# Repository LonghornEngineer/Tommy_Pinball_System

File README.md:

Tommy_Pinball_System
====================

A Pinball System based off the Parallax Propeller. Aimed at hobby use. This project is mothballed. See the PinHeck for future development.

More information can be found on the Tommy project page.

http://longhornengineer.com/pinball/tommy-pinball-system/

Created by:
Parker Dillmann
The Longhorn Engineer

http://longhornengineer.com/

Disclaimer and licensing information can be found below.
http://longhornengineer.com/diy/disclaimer/

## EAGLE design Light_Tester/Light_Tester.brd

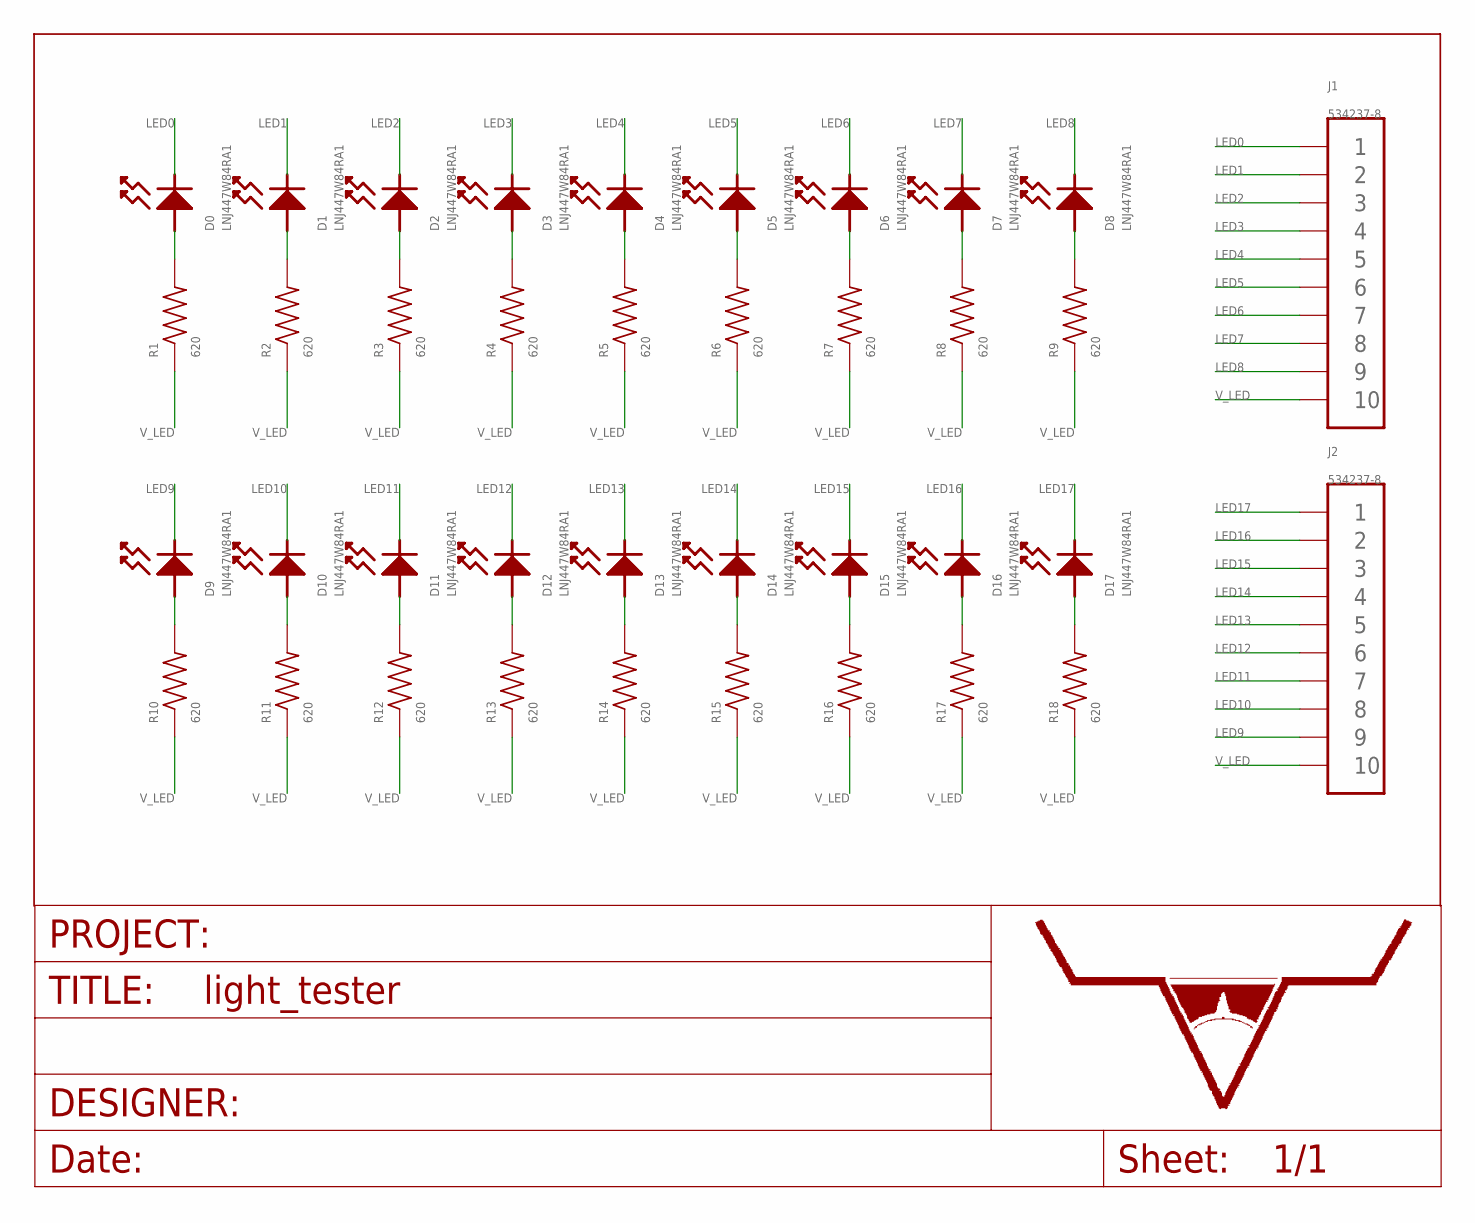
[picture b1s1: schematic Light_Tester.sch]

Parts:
D0, D1, D2, D3, D4, D5, D6, D7, D8, D9, D10, D11, D12, D13, D14, D15, D16, D17: LNJ447W84RA1; LED_0402
J1, J2: 534237-8; HEADER_01X10_PTH
R1, R2, R3, R4, R5, R6, R7, R8, R9, R10, R11, R12, R13, R14, R15, R16, R17, R18: 620; 0402
U$1: LHE_FRAME

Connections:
LED0: D0.CATHODE, J1.1
LED1: D1.CATHODE, J1.2
LED2: D2.CATHODE, J1.3
LED3: D3.CATHODE, J1.4
LED4: D4.CATHODE, J1.5
LED5: D5.CATHODE, J1.6
LED6: D6.CATHODE, J1.7
LED7: D7.CATHODE, J1.8
LED8: D8.CATHODE, J1.9
LED9: D9.CATHODE, J2.9
LED10: D10.CATHODE, J2.8
LED11: D11.CATHODE, J2.7
LED12: D12.CATHODE, J2.6
LED13: D13.CATHODE, J2.5
LED14: D14.CATHODE, J2.4
LED15: D15.CATHODE, J2.3
LED16: D16.CATHODE, J2.2
LED17: D17.CATHODE, J2.1
unnamed: D1.ANODE, R2.2
unnamed: D0.ANODE, R1.2
unnamed: D2.ANODE, R3.2
unnamed: D3.ANODE, R4.2
unnamed: D4.ANODE, R5.2
unnamed: D5.ANODE, R6.2
unnamed: D6.ANODE, R7.2
unnamed: D7.ANODE, R8.2
unnamed: D8.ANODE, R9.2
unnamed: D9.ANODE, R10.2
unnamed: D10.ANODE, R11.2
unnamed: D11.ANODE, R12.2
unnamed: D12.ANODE, R13.2
unnamed: D13.ANODE, R14.2
unnamed: D14.ANODE, R15.2
unnamed: D15.ANODE, R16.2
unnamed: D16.ANODE, R17.2
unnamed: D17.ANODE, R18.2
V_LED: J1.10, J2.10, R1.1, R2.1, R3.1, R4.1, R5.1, R6.1, R7.1, R8.1, R9.1, R10.1, R11.1, R12.1, R13.1, R14.1, R15.1, R16.1, R17.1, R18.1

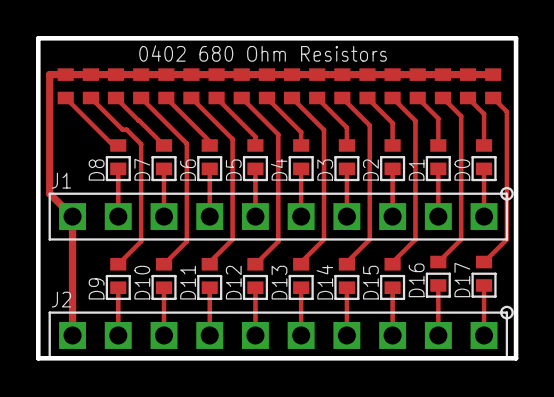
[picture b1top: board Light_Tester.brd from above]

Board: 4 copper layers, 26.5 x 17.8 mm, 39 parts (1 on the bottom side), 37 nets.

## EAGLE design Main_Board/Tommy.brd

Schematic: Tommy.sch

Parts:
ANALOG_0, ANALOG_1, ANALOG_2, ANALOG_3: PH_1X03HEADER_PTH; HEADER_01X03_PTH
AUDIO: 161-3507-E
AUX: 103169-5; HEADER_02X07_PTH
C1, C2, C3, C4, C5, C6, C7, C8, C9, C10, C11, C12, C13, C14, C15, C16, C17, C18, C19, C20, C21, C22, C23, C24, C25, C26, C27, C28, C29, C30, C31, C36, C41, C44, C45, C46, C47, C48, C49, C50, C51, C52, C53, C58, C59, C61: .1uF; 0402
C32, C37, C54: 2.2uF; 1206_POLARIZED
C33, C38, C55: 10uF; 1206_POLARIZED
C34, C39, C56, C65: 100uF; 6.3MM_CAP_SMD
C35, C40, C42, C43, C57, C60, C66, C67, C68, C69: 1uF; 0402
C62, C63, C64: ULR2C390MNL1GS; EEH-ZA1V271P
D1, D2, D3, D4, D5: LEDSML0603; SML0603
DMD_CONN: 103169-5; HEADER_02X07_PTH
DMD_PWR: PH_1X02MOLEX_26-61-4020; MOLEX_KK_2
EM1: SPDT_RELAYG5LA; G5LA_PCBRELAY_SPDT
FUSE: 4245K
INPUT_BANK_0, INPUT_BANK_1, INPUT_BANK_2, INPUT_BANK_3, INPUT_BANK_4, INPUT_BANK_5, INPUT_BANK_6, INPUT_BANK_7: 5-103669-8; HEADER_01X09_PTH
J35, J36: ROYS_VOLTAGE_CHOOSER
LIGHT_BANK_0, LIGHT_BANK_1, LIGHT_BANK_2, LIGHT_BANK_3, LIGHT_BANK_4, LIGHT_BANK_5, LIGHT_BANK_6, LIGHT_BANK_7: 103414-8; HEADER_01X10_PTH
OUTPUT_BANK_0, OUTPUT_BANK_1, OUTPUT_BANK_2, OUTPUT_BANK_3: 26-61-4090; MOLEX_KK_9
PC_POWER_SUPPLY: MOLEX_39-29-9202
R1, R2, R3, R186, R187: 330; 0402
R4, R5, R6, R7, R8, R9, R10, R11, R15, R16, R17, R18, R19, R20, R21, R22, R23, R24, R25, R26, R27, R28, R29, R30, R31, R32, R33, R34, R35, R36, R37, R38, R39, R40, R41, R42, R43, R44, R45, R46, R176, R179, R189: 10K; 0402
R12, R13, R14, R175: 1.25K; 0402
R47, R48, R49, R50, R55, R56, R57, R58, R63, R64, R65, R66, R71, R72, R73, R74, R79, R80, R81, R82, R87, R88, R89, R90, R95, R96, R97, R98, R103, R104, R105, R106, R111, R112, R113, R114, R119, R120, R121, R122, R127, R128, R129, R130, R135, R136, R137, R138, R143, R144, R145, R146, R151, R152, R153, R154, R159, R160, R161, R162, R167, R168, R169, R170: 180; 0402
R51, R52, R53, R54, R59, R60, R61, R62, R67, R68, R69, R70, R75, R76, R77, R78, R83, R84, R85, R86, R91, R92, R93, R94, R99, R100, R101, R102, R107, R108, R109, R110, R115, R116, R117, R118, R123, R124, R125, R126, R131, R132, R133, R134, R139, R140, R141, R142, R147, R148, R149, R150, R155, R156, R157, R158, R163, R164, R165, R166, R171, R172, R173, R174: 100; 0402
R177, R178, R188: 1K; 0402
R180, R181: 22; 0402
R182, R183: 0; 0402
RESET: 101-0134-EV
RGB_CONN: PH_1X04HEADER_PTH_ROUND; HEADER_01X04_PTH_ROUND
S0, S1, S2, S3, S4, S5, S6, S7, S8, S9, S10, S11, S12, S13, S14, S15, S16, S17, S18, S19, S20, S21, S22, S23, S24, S25, S26, S27, S28, S29, S30, S31: RFP12N10L; TO-220AB
SD1: 502570-0893
SEG1, SEG2, SEG3: LSHD-A103
SERVO_0, SERVO_1, SERVO_2, SERVO_3, SERVO_4, SERVO_5, SERVO_6, SERVO_7: PH_1X03HEADER_PTH; HEADER_01X03_PTH
SERVO_EXT_PWR: 26-61-4020; MOLEX_KK_2
SOLENOID_PWR: 26-61-4020; MOLEX_KK_4
SW2: 0S102011MS2QS1
U1: P8X32A-Q44; LQFP-44
U2: FT230X; SSOP-16
U3, U75, U76, U77, U78, U79, U80, U82: IP4234CZ6; SOT-457
U4: CAT24M01XI-T2; SOIC-8_W
U5, U6, U7, U8, U39, U40, U41, U42: 74HC595D-Q100; TTSOP-16
U9, U10, U11, U12, U13, U14, U15, U16: SN74HC165QPWRG4Q1; TTSOP-16
U17, U18, U19, U38: WS2803; SOP-28
U20, U21, U22, U23, U24, U25, U26, U27, U28, U29, U30, U31, U32, U33, U34, U35: TCMT4100; SOP-16
U36, U37: 23LC1024-I/ST; TTSOP-8
U81: MIC1832MY; SOIC-8
U83: AD7991YRJZ-0500RL7; SOT-23-8
U84: MMBT 3904 LT1; SOT-23
U$1: LHE_FRAME
USB: 10118193-0001LF
X1: ABMM-6.000MHZ-B2-T; 7MM_X_5MM

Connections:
3.3V: ANALOG_0.3, ANALOG_1.3, ANALOG_2.3, ANALOG_3.3, AUX.1, C3.2, C4.2, C5.2, C6.2, C8.2, C9.2, C10.2, C11.2, C12.2, C13.2, C14.2, C15.2, C16.2, C17.2, C18.2, C19.2, C20.2, C21.1, C22.2, C23.2, C24.2, C25.2, C26.2, C27.2, C28.2, C29.2, C30.2, C31.2, C32.+ (POS), C33.+ (POS), C34.POS, C35.1, C36.1, C59.2, C60.2, C61.2, EM1.2, J35.1, PC_POWER_SUPPLY.1, PC_POWER_SUPPLY.2, PC_POWER_SUPPLY.3, R4.2, R5.2, R6.2, R7.2, R8.2, R9.2, R10.2, R11.2, R176.2, R186.2, RGB_CONN.4, SD1.5 (3.3V), U1.8 (VDD), U1.18 (VDD), U1.30 (VDD), U1.40 (VDD), U4.8 (VCC), U5.10 (MR), U5.16 (VCC), U6.10 (MR), U6.16 (VCC), U7.10 (MR), U7.16 (VCC), U8.10 (MR), U8.16 (VCC), U9.16 (VCC), U10.16 (VCC), U11.16 (VCC), U12.16 (VCC), U13.16 (VCC), U14.16 (VCC), U15.16 (VCC), U16.16 (VCC), U17.28 (VCC), U18.28 (VCC), U19.28 (VCC), U20.10 (CO3), U20.12 (CO2), U20.14 (CO1), U20.16 (CO0), U21.10 (CO3), U21.12 (CO2), U21.14 (CO1), U21.16 (CO0), U22.10 (CO3), U22.12 (CO2), U22.14 (CO1), U22.16 (CO0), U23.10 (CO3), U23.12 (CO2), U23.14 (CO1), U23.16 (CO0), U24.10 (CO3), U24.12 (CO2), U24.14 (CO1), U24.16 (CO0), U25.10 (CO3), U25.12 (CO2), U25.14 (CO1), U25.16 (CO0), U26.10 (CO3), U26.12 (CO2), U26.14 (CO1), U26.16 (CO0), U27.10 (CO3), U27.12 (CO2), U27.14 (CO1), U27.16 (CO0), U28.10 (CO3), U28.12 (CO2), U28.14 (CO1), U28.16 (CO0), U29.10 (CO3), U29.12 (CO2), U29.14 (CO1), U29.16 (CO0), U30.10 (CO3), U30.12 (CO2), U30.14 (CO1), U30.16 (CO0), U31.10 (CO3), U31.12 (CO2), U31.14 (CO1), U31.16 (CO0), U32.10 (CO3), U32.12 (CO2), U32.14 (CO1), U32.16 (CO0), U33.10 (CO3), U33.12 (CO2), U33.14 (CO1), U33.16 (CO0), U34.10 (CO3), U34.12 (CO2), U34.14 (CO1), U34.16 (CO0), U35.10 (CO3), U35.12 (CO2), U35.14 (CO1), U35.16 (CO0), U36.8 (VCC), U37.8 (VCC), U38.28 (VCC), U39.10 (MR), U39.16 (VCC), U40.10 (MR), U40.16 (VCC), U41.10 (MR), U41.16 (VCC), U42.10 (MR), U42.16 (VCC), U75.5 (VB), U76.5 (VB), U77.5 (VB), U78.5 (VB), U79.5 (VB), U80.5 (VB), U81.2 (TD), U81.3 (TOL), U81.8 (VCC), U82.5 (VB), U83.8 (VCC)
3V3OUT: C2.1, U2.3 (VCCIO), U2.10 (3V3OUT), U2.11 (RESET#)
5V: C37.+ (POS), C38.+ (POS), C39.POS, C40.1, C41.1, DMD_PWR.P$2 (2), J35.2, J36.1, PC_POWER_SUPPLY.7, PC_POWER_SUPPLY.11, PC_POWER_SUPPLY.18, PC_POWER_SUPPLY.20
12V: C46.2, C47.2, C48.2, C49.2, C50.2, C51.2, C52.2, C53.2, C54.+ (POS), C55.+ (POS), C56.POS, C57.1, C58.1, INPUT_BANK_0.9, INPUT_BANK_1.9, INPUT_BANK_2.9, INPUT_BANK_3.9, INPUT_BANK_4.9, INPUT_BANK_5.9, INPUT_BANK_6.9, INPUT_BANK_7.9, J35.3, J36.3, PC_POWER_SUPPLY.19
-5V: PC_POWER_SUPPLY.16
-12V: PC_POWER_SUPPLY.4
AUDIO_L: R177.1, U1.33 (P26)
AUDIO_OUT_L: AUDIO.5 (T), C42.1
AUDIO_OUT_R: AUDIO.2 (R), C43.1
AUDIO_R: R178.1, U1.34 (P27)
AUD_L_FILTER: C42.2, C44.1, R177.2
AUD_R_FILTER: C43.2, C45.2, R178.2
A_0: ANALOG_0.1, U83.3 (A_0)
A_1: ANALOG_1.1, U83.4 (A_1)
A_2: ANALOG_2.1, U83.5 (A_2)
A_3: ANALOG_3.1, U83.6 (A_3)
C0: R47.1, U20.2 (C0)
C1: R48.1, U20.4 (C1)
C2: R49.1, U20.6 (C2)
C3: R50.1, U20.8 (C3)
C4: R55.1, U21.2 (C0)
C5: R56.1, U21.4 (C1)
C6: R57.1, U21.6 (C2)
C7: R58.1, U21.8 (C3)
C8: R63.1, U22.2 (C0)
C9: R64.1, U22.4 (C1)
C10: R65.1, U22.6 (C2)
C11: R66.1, U22.8 (C3)
C12: R71.1, U23.2 (C0)
C13: R72.1, U23.4 (C1)
C14: R73.1, U23.6 (C2)
C15: R74.1, U23.8 (C3)
C16: R79.1, U24.2 (C0)
C17: R80.1, U24.4 (C1)
C18: R81.1, U24.6 (C2)
C19: R82.1, U24.8 (C3)
C20: R87.1, U25.2 (C0)
C21: R88.1, U25.4 (C1)
C22: R89.1, U25.6 (C2)
C23: R90.1, U25.8 (C3)
C24: R95.1, U26.2 (C0)
C25: R96.1, U26.4 (C1)
C26: R97.1, U26.6 (C2)
C27: R98.1, U26.8 (C3)
C28: R103.1, U27.2 (C0)
C29: R104.1, U27.4 (C1)
C30: R105.1, U27.6 (C2)
C31: R106.1, U27.8 (C3)
C32: R111.1, U28.2 (C0)
C33: R112.1, U28.4 (C1)
C34: R113.1, U28.6 (C2)
C35: R114.1, U28.8 (C3)
C36: R119.1, U29.2 (C0)
C37: R120.1, U29.4 (C1)
C38: R121.1, U29.6 (C2)
C39: R122.1, U29.8 (C3)
C40: R127.1, U30.2 (C0)
C41: R128.1, U30.4 (C1)
C42: R129.1, U30.6 (C2)
C43: R130.1, U30.8 (C3)
C44: R135.1, U31.2 (C0)
C45: R136.1, U31.4 (C1)
C46: R137.1, U31.6 (C2)
C47: R138.1, U31.8 (C3)
C48: R143.1, U32.2 (C0)
C49: R144.1, U32.4 (C1)
C50: R145.1, U32.6 (C2)
C51: R146.1, U32.8 (C3)
C52: R151.1, U33.2 (C0)
C53: R152.1, U33.4 (C1)
C54: R153.1, U33.6 (C2)
C55: R154.1, U33.8 (C3)
C56: R159.1, U34.2 (C0)
C57: R160.1, U34.4 (C1)
C58: R161.1, U34.6 (C2)
C59: R162.1, U34.8 (C3)
C60: R167.1, U35.2 (C0)
C61: R168.1, U35.4 (C1)
C62: R169.1, U35.6 (C2)
C63: R170.1, U35.8 (C3)
D1: D1.C, R1.2
D2: D2.C, R2.2
D3: D3.C, R3.2
D+: U3.1 (I/O1A), USB.3 (D+)
D-: U3.6 (I/O1B), USB.2 (D-)
DATA_CLK: U1.3 (P6), U5.12 (STCP), U6.12 (STCP), U7.12 (STCP), U8.12 (STCP), U9.2 (CLK), U10.2 (CLK), U11.2 (CLK), U12.2 (CLK), U13.2 (CLK), U14.2 (CLK), U15.2 (CLK), U16.2 (CLK), U39.12 (STCP), U40.12 (STCP), U41.12 (STCP), U42.12 (STCP), U80.4 (I/O2B), U81.7 (/ST)
DATA_CLK_OUT: AUX.3, U80.6 (I/O1B)
DATA_IN: U1.2 (P5), U9.9 (QH)
DATA_IN1: U9.10 (SER), U10.9 (QH)
DATA_IN2: U10.10 (SER), U11.9 (QH)
DATA_IN3: U11.10 (SER), U12.9 (QH)
DATA_IN4: U12.10 (SER), U13.9 (QH)
DATA_IN5: U13.10 (SER), U14.9 (QH)
DATA_IN6: U14.10 (SER), U15.9 (QH)
DATA_IN7: U15.10 (SER), U16.9 (QH)
DATA_IN8: U16.10 (SER), U79.4 (I/O2B)
DATA_IN8_OUT: AUX.5, U79.6 (I/O1B)
DATA_LAT: U1.4 (P7), U5.11 (SHCP), U6.11 (SHCP), U7.11 (SHCP), U8.11 (SHCP), U9.1 (LAT), U10.1 (LAT), U11.1 (LAT), U12.1 (LAT), U13.1 (LAT), U14.1 (LAT), U15.1 (LAT), U16.1 (LAT), U39.11 (SHCP), U40.11 (SHCP), U41.11 (SHCP), U42.11 (SHCP), U80.3 (I/O2A)
DATA_LAT_OUT: AUX.2, U80.1 (I/O1A)
DATA_OUT: U1.1 (P4), U5.14 (DS)
DATA_OUT1: U5.9 (Q7S), U6.14 (DS)
DATA_OUT2: U6.9 (Q7S), U7.14 (DS)
DATA_OUT3: U7.9 (Q7S), U8.14 (DS)
DATA_OUT4: U8.9 (Q7S), U39.14 (DS)
DATA_OUT5: U39.9 (Q7S), U40.14 (DS)
DATA_OUT6: U40.9 (Q7S), U41.14 (DS)
DATA_OUT7: U41.9 (Q7S), U42.14 (DS)
DATA_OUT8: U42.9 (Q7S), U79.3 (I/O2A)
DATA_OUT8_OUT: AUX.4, U79.1 (I/O1A)
DM: R180.2, U3.4 (I/O2B)
DMD0: U1.14 (P13), U78.3 (I/O2A)
DMD1: U1.13 (P12), U78.4 (I/O2B)
DMD2: U1.12 (P11), U77.3 (I/O2A)
DMD3: U1.11 (P10), U77.4 (I/O2B)
DMD4: U1.10 (P9), U76.3 (I/O2A)
DMD5: U1.9 (P8), U76.4 (I/O2B)
DMD_OUT0: DMD_CONN.1, U78.1 (I/O1A)
DMD_OUT1: DMD_CONN.2, U78.6 (I/O1B)
DMD_OUT2: DMD_CONN.3, U77.1 (I/O1A)
DMD_OUT3: DMD_CONN.4, U77.6 (I/O1B)
DMD_OUT4: DMD_CONN.5, U76.1 (I/O1A)
DMD_OUT5: DMD_CONN.6, U76.6 (I/O1B)
DP: R181.2, U3.3 (I/O2A)
GND: ANALOG_0.2, ANALOG_1.2, ANALOG_2.2, ANALOG_3.2, AUDIO.1 (S), AUX.8, AUX.9, AUX.10, AUX.11, AUX.12, AUX.13, AUX.14, C1.2, C2.2, C3.1, C4.1, C5.1, C6.1, C8.1, C9.1, C10.1, C11.1, C12.1, C13.1, C14.1, C15.1, C16.1, C17.1, C18.1, C19.1, C20.1, C21.2, C22.1, C23.1, C24.1, C25.1, C26.1, C27.1, C28.1, C29.1, C30.1, C31.1, C32.- (NEG), C33.- (NEG), C34.NEG, C35.2, C36.2, C37.- (NEG), C38.- (NEG), C39.NEG, C40.2, C41.2, C44.2, C45.1, C46.1, C47.1, C48.1, C49.1, C50.1, C51.1, C52.1, C53.1, C54.- (NEG), C55.- (NEG), C56.NEG, C57.2, C58.2, C59.1, C60.1, C61.1, C65.NEG, C66.1, C67.1, C68.1, C69.1, D4.C, DMD_CONN.8, DMD_CONN.9, DMD_CONN.10, DMD_CONN.11, DMD_CONN.12, DMD_CONN.13, DMD_CONN.14, DMD_PWR.P$1 (1), PC_POWER_SUPPLY.5, PC_POWER_SUPPLY.6, PC_POWER_SUPPLY.9, PC_POWER_SUPPLY.10, PC_POWER_SUPPLY.12, PC_POWER_SUPPLY.13, PC_POWER_SUPPLY.14, R1.1, R12.2, R13.2, R14.2, R15.1, R16.1, R17.1, R18.1, R19.1, R20.1, R21.1, R22.1, R23.1, R24.1, R25.1, R26.1, R27.1, R28.1, R29.1, R30.1, R31.1, R32.1, R33.1, R34.1, R35.1, R36.1, R37.1, R38.1, R39.1, R40.1, R41.1, R42.1, R43.1, R44.1, R45.1, R46.1, R47.2, R48.2, R49.2, R50.2, R51.1, R52.1, R53.1, R54.1, R55.2, R56.2, R57.2, R58.2, R59.1, R60.1, R61.1, R62.1, R63.2, R64.2, R65.2, R66.2, R67.1, R68.1, R69.1, R70.1, R71.2, R72.2, R73.2, R74.2, R75.1, R76.1, R77.1, R78.1, R79.2, R80.2, R81.2, R82.2, R83.1, R84.1, R85.1, R86.1, R87.2, R88.2, R89.2, R90.2, R91.1, R92.1, R93.1, R94.1, R95.2, R96.2, R97.2, R98.2, R99.1, R100.1, R101.1, R102.1, R103.2, R104.2, R105.2, R106.2, R107.1, R108.1, R109.1, R110.1, R111.2, R112.2, R113.2, R114.2, R115.1, R116.1, R117.1, R118.1, R119.2, R120.2, R121.2, R122.2, R123.1, R124.1, R125.1, R126.1, R127.2, R128.2, R129.2, R130.2, R131.1, R132.1, R133.1, R134.1, R135.2, R136.2, R137.2, R138.2, R139.1, R140.1, R141.1, R142.1, R143.2, R144.2, R145.2, R146.2, R147.1, R148.1, R149.1, R150.1, R151.2, R152.2, R153.2, R154.2, R155.1, R156.1, R157.1, R158.1, R159.2, R160.2, R161.2, R162.2, R163.1, R164.1, R165.1, R166.1, R167.2, R168.2, R169.2, R170.2, R171.1, R172.1, R173.1, R174.1, R175.2, R179.2, R182.2, R183.2, R187.1, R189.2, RESET.1 (A), RGB_CONN.3, SD1.3 (GND), SD1.SHIELD0 (GND), SD1.SHIELD1 (GND), SD1.SHIELD2 (GND), SD1.SHIELD3 (GND), SEG1.1 (COM), SEG1.6 (COM), SEG2.1 (COM), SEG2.6 (COM), SEG3.1 (COM), SEG3.6 (COM), SERVO_0.3, SERVO_1.3, SERVO_2.3, SERVO_3.3, SERVO_4.3, SERVO_5.3, SERVO_6.3, SERVO_7.3, SERVO_EXT_PWR.P$1 (1), SW2.1, U1.5 (VSS), U1.6 (BOE'), U1.17 (VSS), U1.27 (VSS), U1.39 (VSS), U2.5 (GND), U2.13 (GND), U3.2 (GND), U4.2 (A1), U4.3 (A2), U4.4 (GND), U4.7 (WP), U5.8 (GND), U6.8 (GND), U7.8 (GND), U8.8 (GND), U9.8 (GND), U9.15 (C_INH), U10.8 (GND), U10.15 (C_INH), U11.8 (GND), U11.15 (C_INH), U12.8 (GND), U12.15 (C_INH), U13.8 (GND), U13.15 (C_INH), U14.8 (GND), U14.15 (C_INH), U15.8 (GND), U15.15 (C_INH), U16.8 (GND), U16.15 (C_INH), U17.1 (GND), U18.1 (GND), U19.1 (GND), U36.1 (CS'), U36.4 (GND), U37.1 (CS'), U37.4 (GND), U38.1 (GND), U39.8 (GND), U40.8 (GND), U41.8 (GND), U42.8 (GND), U75.2 (GND), U76.2 (GND), U77.2 (GND), U78.2 (GND), U79.2 (GND), U80.2 (GND), U81.4 (GND), U82.2 (GND), U83.7 (GND), U84.2 (EMITTER), USB.5 (GND), USB.S1 (GND), USB.S2 (GND), USB.S3 (GND), USB.S4 (GND)
IN0: R51.2, U9.11 (D0), U20.15 (E0)
IN1: R52.2, U9.12 (D1), U20.13 (E1)
IN2: R53.2, U9.13 (D2), U20.11 (E2)
IN3: R54.2, U9.14 (D3), U20.9 (E3)
IN4: R59.2, U9.3 (D4), U21.15 (E0)
IN5: R60.2, U9.4 (D5), U21.13 (E1)
IN6: R61.2, U9.5 (D6), U21.11 (E2)
IN7: R62.2, U9.6 (D7), U21.9 (E3)
IN8: R67.2, U10.11 (D0), U22.15 (E0)
IN9: R68.2, U10.12 (D1), U22.13 (E1)
IN10: R69.2, U10.13 (D2), U22.11 (E2)
IN11: R70.2, U10.14 (D3), U22.9 (E3)
IN12: R75.2, U10.3 (D4), U23.15 (E0)
IN13: R76.2, U10.4 (D5), U23.13 (E1)
IN14: R77.2, U10.5 (D6), U23.11 (E2)
IN15: R78.2, U10.6 (D7), U23.9 (E3)
IN16: R83.2, U11.11 (D0), U24.15 (E0)
IN17: R84.2, U11.12 (D1), U24.13 (E1)
IN18: R85.2, U11.13 (D2), U24.11 (E2)
IN19: R86.2, U11.14 (D3), U24.9 (E3)
IN20: R91.2, U11.3 (D4), U25.15 (E0)
IN21: R92.2, U11.4 (D5), U25.13 (E1)
IN22: R93.2, U11.5 (D6), U25.11 (E2)
IN23: R94.2, U11.6 (D7), U25.9 (E3)
IN24: R99.2, U12.11 (D0), U26.15 (E0)
IN25: R100.2, U12.12 (D1), U26.13 (E1)
IN26: R101.2, U12.13 (D2), U26.11 (E2)
IN27: R102.2, U12.14 (D3), U26.9 (E3)
IN28: R107.2, U12.3 (D4), U27.15 (E0)
IN29: R108.2, U12.4 (D5), U27.13 (E1)
IN30: R109.2, U12.5 (D6), U27.11 (E2)
IN31: R110.2, U12.6 (D7), U27.9 (E3)
IN32: R115.2, U13.11 (D0), U28.15 (E0)
IN33: R116.2, U13.12 (D1), U28.13 (E1)
IN34: R117.2, U13.13 (D2), U28.11 (E2)
IN35: R118.2, U13.14 (D3), U28.9 (E3)
IN36: R123.2, U13.3 (D4), U29.15 (E0)
IN37: R124.2, U13.4 (D5), U29.13 (E1)
IN38: R125.2, U13.5 (D6), U29.11 (E2)
IN39: R126.2, U13.6 (D7), U29.9 (E3)
IN40: R131.2, U14.11 (D0), U30.15 (E0)
IN41: R132.2, U14.12 (D1), U30.13 (E1)
IN42: R133.2, U14.13 (D2), U30.11 (E2)
IN43: R134.2, U14.14 (D3), U30.9 (E3)
IN44: R139.2, U14.3 (D4), U31.15 (E0)
IN45: R140.2, U14.4 (D5), U31.13 (E1)
IN46: R141.2, U14.5 (D6), U31.11 (E2)
IN47: R142.2, U14.6 (D7), U31.9 (E3)
IN48: R147.2, U15.11 (D0), U32.15 (E0)
IN49: R148.2, U15.12 (D1), U32.13 (E1)
IN50: R149.2, U15.13 (D2), U32.11 (E2)
IN51: R150.2, U15.14 (D3), U32.9 (E3)
IN52: R155.2, U15.3 (D4), U33.15 (E0)
IN53: R156.2, U15.4 (D5), U33.13 (E1)
IN54: R157.2, U15.5 (D6), U33.11 (E2)
IN55: R158.2, U15.6 (D7), U33.9 (E3)
IN56: R163.2, U16.11 (D0), U34.15 (E0)
IN57: R164.2, U16.12 (D1), U34.13 (E1)
IN58: R165.2, U16.13 (D2), U34.11 (E2)
IN59: R166.2, U16.14 (D3), U34.9 (E3)
IN60: R171.2, U16.3 (D4), U35.15 (E0)
IN61: R172.2, U16.4 (D5), U35.13 (E1)
IN62: R173.2, U16.5 (D6), U35.11 (E2)
IN63: R174.2, U16.6 (D7), U35.9 (E3)
INPUT0: INPUT_BANK_0.1, U20.1 (A0)
INPUT1: INPUT_BANK_0.2, U20.3 (A1)
INPUT2: INPUT_BANK_0.3, U20.5 (A2)
INPUT3: INPUT_BANK_0.4, U20.7 (A3)
INPUT4: INPUT_BANK_0.5, U21.1 (A0)
INPUT5: INPUT_BANK_0.6, U21.3 (A1)
INPUT6: INPUT_BANK_0.7, U21.5 (A2)
INPUT7: INPUT_BANK_0.8, U21.7 (A3)
INPUT8: INPUT_BANK_1.1, U22.1 (A0)
INPUT9: INPUT_BANK_1.2, U22.3 (A1)
INPUT10: INPUT_BANK_1.3, U22.5 (A2)
INPUT11: INPUT_BANK_1.4, U22.7 (A3)
INPUT12: INPUT_BANK_1.5, U23.1 (A0)
INPUT13: INPUT_BANK_1.6, U23.3 (A1)
INPUT14: INPUT_BANK_1.7, U23.5 (A2)
INPUT15: INPUT_BANK_1.8, U23.7 (A3)
INPUT16: INPUT_BANK_2.1, U24.1 (A0)
INPUT17: INPUT_BANK_2.2, U24.3 (A1)
INPUT18: INPUT_BANK_2.3, U24.5 (A2)
INPUT19: INPUT_BANK_2.4, U24.7 (A3)
INPUT20: INPUT_BANK_2.5, U25.1 (A0)
INPUT21: INPUT_BANK_2.6, U25.3 (A1)
INPUT22: INPUT_BANK_2.7, U25.5 (A2)
INPUT23: INPUT_BANK_2.8, U25.7 (A3)
INPUT24: INPUT_BANK_3.1, U26.1 (A0)
INPUT25: INPUT_BANK_3.2, U26.3 (A1)
INPUT26: INPUT_BANK_3.3, U26.5 (A2)
INPUT27: INPUT_BANK_3.4, U26.7 (A3)
INPUT28: INPUT_BANK_3.5, U27.1 (A0)
INPUT29: INPUT_BANK_3.6, U27.3 (A1)
INPUT30: INPUT_BANK_3.7, U27.5 (A2)
INPUT31: INPUT_BANK_3.8, U27.7 (A3)
INPUT32: INPUT_BANK_4.1, U28.1 (A0)
INPUT33: INPUT_BANK_4.2, U28.3 (A1)
INPUT34: INPUT_BANK_4.3, U28.5 (A2)
INPUT35: INPUT_BANK_4.4, U28.7 (A3)
INPUT36: INPUT_BANK_4.5, U29.1 (A0)
INPUT37: INPUT_BANK_4.6, U29.3 (A1)
INPUT38: INPUT_BANK_4.7, U29.5 (A2)
INPUT39: INPUT_BANK_4.8, U29.7 (A3)
INPUT40: INPUT_BANK_5.1, U30.1 (A0)
INPUT41: INPUT_BANK_5.2, U30.3 (A1)
INPUT42: INPUT_BANK_5.3, U30.5 (A2)
INPUT43: INPUT_BANK_5.4, U30.7 (A3)
INPUT44: INPUT_BANK_5.5, U31.1 (A0)
INPUT45: INPUT_BANK_5.6, U31.3 (A1)
INPUT46: INPUT_BANK_5.7, U31.5 (A2)
INPUT47: INPUT_BANK_5.8, U31.7 (A3)
INPUT48: INPUT_BANK_6.1, U32.1 (A0)
INPUT49: INPUT_BANK_6.2, U32.3 (A1)
INPUT50: INPUT_BANK_6.3, U32.5 (A2)
INPUT51: INPUT_BANK_6.4, U32.7 (A3)
INPUT52: INPUT_BANK_6.5, U33.1 (A0)
INPUT53: INPUT_BANK_6.6, U33.3 (A1)
INPUT54: INPUT_BANK_6.7, U33.5 (A2)
INPUT55: INPUT_BANK_6.8, U33.7 (A3)
INPUT56: INPUT_BANK_7.1, U34.1 (A0)
INPUT57: INPUT_BANK_7.2, U34.3 (A1)
INPUT58: INPUT_BANK_7.3, U34.5 (A2)
INPUT59: INPUT_BANK_7.4, U34.7 (A3)
INPUT60: INPUT_BANK_7.5, U35.1 (A0)
INPUT61: INPUT_BANK_7.6, U35.3 (A1)
INPUT62: INPUT_BANK_7.7, U35.5 (A2)
INPUT63: INPUT_BANK_7.8, U35.7 (A3)
IREF0: R12.1, U17.3 (IREF)
IREF1: R13.1, U18.3 (IREF)
IREF2: R14.1, U19.3 (IREF)
IREF3: R175.1, U38.3 (IREF)
IRQ: R6.1, SD1.1 (IRQ)
LED0: LIGHT_BANK_0.1, U17.6 (OUT0)
LED1: LIGHT_BANK_0.2, U17.7 (OUT1)
LED2: LIGHT_BANK_0.3, U17.8 (OUT2)
LED3: LIGHT_BANK_0.4, U17.9 (OUT3)
LED4: LIGHT_BANK_0.5, U17.10 (OUT4)
LED5: LIGHT_BANK_0.6, U17.11 (OUT5)
LED6: LIGHT_BANK_0.7, U17.12 (OUT6)
LED7: LIGHT_BANK_0.8, U17.13 (OUT7)
LED8: LIGHT_BANK_0.9, U17.14 (OUT8)
LED9: LIGHT_BANK_1.9, U17.15 (OUT9)
LED10: LIGHT_BANK_1.8, U17.16 (OUT10)
LED11: LIGHT_BANK_1.7, U17.17 (OUT11)
LED12: LIGHT_BANK_1.6, U17.18 (OUT12)
LED13: LIGHT_BANK_1.5, U17.19 (OUT13)
LED14: LIGHT_BANK_1.4, U17.20 (OUT14)
LED15: LIGHT_BANK_1.3, U17.21 (OUT15)
LED16: LIGHT_BANK_1.2, U17.22 (OUT16)
LED17: LIGHT_BANK_1.1, U17.23 (OUT17)
LED18: LIGHT_BANK_2.1, U18.6 (OUT0)
LED19: LIGHT_BANK_2.2, U18.7 (OUT1)
LED20: LIGHT_BANK_2.3, U18.8 (OUT2)
LED21: LIGHT_BANK_2.4, U18.9 (OUT3)
LED22: LIGHT_BANK_2.5, U18.10 (OUT4)
LED23: LIGHT_BANK_2.6, U18.11 (OUT5)
LED24: LIGHT_BANK_2.7, U18.12 (OUT6)
LED25: LIGHT_BANK_2.8, U18.13 (OUT7)
LED26: LIGHT_BANK_2.9, U18.14 (OUT8)
LED27: LIGHT_BANK_3.9, U18.15 (OUT9)
LED28: LIGHT_BANK_3.8, U18.16 (OUT10)
LED29: LIGHT_BANK_3.7, U18.17 (OUT11)
LED30: LIGHT_BANK_3.6, U18.18 (OUT12)
LED31: LIGHT_BANK_3.5, U18.19 (OUT13)
LED32: LIGHT_BANK_3.4, U18.20 (OUT14)
LED33: LIGHT_BANK_3.3, U18.21 (OUT15)
LED34: LIGHT_BANK_3.2, U18.22 (OUT16)
LED35: LIGHT_BANK_3.1, U18.23 (OUT17)
LED36: LIGHT_BANK_4.1, U19.6 (OUT0)
LED37: LIGHT_BANK_4.2, U19.7 (OUT1)
LED38: LIGHT_BANK_4.3, U19.8 (OUT2)
LED39: LIGHT_BANK_4.4, U19.9 (OUT3)
LED40: LIGHT_BANK_4.5, U19.10 (OUT4)
LED41: LIGHT_BANK_4.6, U19.11 (OUT5)
LED42: LIGHT_BANK_4.7, U19.12 (OUT6)
LED43: LIGHT_BANK_4.8, U19.13 (OUT7)
LED44: LIGHT_BANK_4.9, U19.14 (OUT8)
LED45: LIGHT_BANK_5.9, U19.15 (OUT9)
LED46: LIGHT_BANK_5.8, U19.16 (OUT10)
LED47: LIGHT_BANK_5.7, U19.17 (OUT11)
LED48: LIGHT_BANK_5.6, U19.18 (OUT12)
LED49: LIGHT_BANK_5.5, U19.19 (OUT13)
LED50: LIGHT_BANK_5.4, U19.20 (OUT14)
LED51: LIGHT_BANK_5.3, U19.21 (OUT15)
LED52: LIGHT_BANK_5.2, U19.22 (OUT16)
LED53: LIGHT_BANK_5.1, U19.23 (OUT17)
LED54: LIGHT_BANK_6.1, U38.6 (OUT0)
LED55: LIGHT_BANK_6.2, U38.7 (OUT1)
LED56: LIGHT_BANK_6.3, U38.8 (OUT2)
LED57: LIGHT_BANK_6.4, U38.9 (OUT3)
LED58: LIGHT_BANK_6.5, U38.10 (OUT4)
LED59: LIGHT_BANK_6.6, U38.11 (OUT5)
LED60: LIGHT_BANK_6.7, U38.12 (OUT6)
LED61: LIGHT_BANK_6.8, U38.13 (OUT7)
LED62: LIGHT_BANK_6.9, U38.14 (OUT8)
LED63: LIGHT_BANK_7.9, U38.15 (OUT9)
LED64: LIGHT_BANK_7.8, U38.16 (OUT10)
LED65: LIGHT_BANK_7.7, U38.17 (OUT11)
LED66: LIGHT_BANK_7.6, U38.18 (OUT12)
LED67: LIGHT_BANK_7.5, U38.19 (OUT13)
LED68: LIGHT_BANK_7.4, U38.20 (OUT14)
LED69: LIGHT_BANK_7.3, U38.21 (OUT15)
LED70: LIGHT_BANK_7.2, U38.22 (OUT16)
LED71: LIGHT_BANK_7.1, U38.23 (OUT17)
LED_CK0: U1.32 (P25), U17.4 (CKI)
LED_CK1: U17.25 (CKO), U18.4 (CKI)
LED_CK2: U18.25 (CKO), U19.4 (CKI)
LED_CK3: U19.25 (CKO), U38.4 (CKI)
LED_CK4: U38.25 (CKO), U82.3 (I/O2A)
LED_CK4_OUT: RGB_CONN.1, U82.1 (I/O1A)
LED_SD0: U1.31 (P24), U17.5 (SDI)
LED_SD1: U17.24 (SDO), U18.5 (SDI)
LED_SD2: U18.24 (SDO), U19.5 (SDI)
LED_SD3: U19.24 (SDO), U38.5 (SDI)
LED_SD4: U38.24 (SDO), U82.4 (I/O2B)
LED_SD4_OUT: RGB_CONN.2, U82.6 (I/O1B)
unnamed: R188.2, U84.1 (BASE)
unnamed: D5.C, R187.2
OUT0: R16.2, S0.G (GATE), U5.15 (Q0)
OUT1: R15.2, S1.G (GATE), U5.1 (Q1)
OUT2: R18.2, S2.G (GATE), U5.2 (Q2)
OUT3: R17.2, S3.G (GATE), U5.3 (Q3)
OUT4: R20.2, S4.G (GATE), U5.4 (Q4)
OUT5: R19.2, S5.G (GATE), U5.5 (Q5)
OUT6: R22.2, S6.G (GATE), U5.6 (Q6)
OUT7: R21.2, S7.G (GATE), U5.7 (Q7)
OUT8: R24.2, S8.G (GATE), U6.15 (Q0)
OUT9: R23.2, S9.G (GATE), U6.1 (Q1)
OUT10: R26.2, S10.G (GATE), U6.2 (Q2)
OUT11: R25.2, S11.G (GATE), U6.3 (Q3)
OUT12: R28.2, S12.G (GATE), U6.4 (Q4)
OUT13: R27.2, S13.G (GATE), U6.5 (Q5)
OUT14: R30.2, S14.G (GATE), U6.6 (Q6)
OUT15: R29.2, S15.G (GATE), U6.7 (Q7)
OUT16: R32.2, S16.G (GATE), U7.15 (Q0)
OUT17: R31.2, S17.G (GATE), U7.1 (Q1)
OUT18: R34.2, S18.G (GATE), U7.2 (Q2)
OUT19: R33.2, S19.G (GATE), U7.3 (Q3)
OUT20: R36.2, S20.G (GATE), U7.4 (Q4)
OUT21: R35.2, S21.G (GATE), U7.5 (Q5)
OUT22: R38.2, S22.G (GATE), U7.6 (Q6)
OUT23: R37.2, S23.G (GATE), U7.7 (Q7)
OUT24: R40.2, S24.G (GATE), U8.15 (Q0)
OUT25: R39.2, S25.G (GATE), U8.1 (Q1)
OUT26: R42.2, S26.G (GATE), U8.2 (Q2)
OUT27: R41.2, S27.G (GATE), U8.3 (Q3)
OUT28: R44.2, S28.G (GATE), U8.4 (Q4)
OUT29: R43.2, S29.G (GATE), U8.5 (Q5)
OUT30: R46.2, S30.G (GATE), U8.6 (Q6)
OUT31: R45.2, S31.G (GATE), U8.7 (Q7)
OUTPUT_00: OUTPUT_BANK_0.P$1 (1), S0.D (DRAIN)
OUTPUT_01: OUTPUT_BANK_0.P$2 (2), S1.D (DRAIN)
OUTPUT_02: OUTPUT_BANK_0.P$3 (3), S2.D (DRAIN)
OUTPUT_03: OUTPUT_BANK_0.P$4 (4), S3.D (DRAIN)
OUTPUT_04: OUTPUT_BANK_0.P$5 (5), S4.D (DRAIN)
OUTPUT_05: OUTPUT_BANK_0.P$6 (6), S5.D (DRAIN)
OUTPUT_06: OUTPUT_BANK_0.P$7 (7), S6.D (DRAIN)
OUTPUT_07: OUTPUT_BANK_0.P$8 (8), S7.D (DRAIN)
OUTPUT_08: OUTPUT_BANK_1.P$1 (1), S8.D (DRAIN)
OUTPUT_09: OUTPUT_BANK_1.P$2 (2), S9.D (DRAIN)
OUTPUT_10: OUTPUT_BANK_1.P$3 (3), S10.D (DRAIN)
OUTPUT_11: OUTPUT_BANK_1.P$4 (4), S11.D (DRAIN)
OUTPUT_12: OUTPUT_BANK_1.P$5 (5), S12.D (DRAIN)
OUTPUT_13: OUTPUT_BANK_1.P$6 (6), S13.D (DRAIN)
OUTPUT_14: OUTPUT_BANK_1.P$7 (7), S14.D (DRAIN)
OUTPUT_15: OUTPUT_BANK_1.P$8 (8), S15.D (DRAIN)
OUTPUT_16: OUTPUT_BANK_2.P$1 (1), S16.D (DRAIN)
OUTPUT_17: OUTPUT_BANK_2.P$2 (2), S17.D (DRAIN)
OUTPUT_18: OUTPUT_BANK_2.P$3 (3), S18.D (DRAIN)
OUTPUT_19: OUTPUT_BANK_2.P$4 (4), S19.D (DRAIN)
OUTPUT_20: OUTPUT_BANK_2.P$5 (5), S20.D (DRAIN)
OUTPUT_21: OUTPUT_BANK_2.P$6 (6), S21.D (DRAIN)
OUTPUT_22: OUTPUT_BANK_2.P$7 (7), S22.D (DRAIN)
OUTPUT_23: OUTPUT_BANK_2.P$8 (8), S23.D (DRAIN)
OUTPUT_24: OUTPUT_BANK_3.P$1 (1), S24.D (DRAIN)
OUTPUT_25: OUTPUT_BANK_3.P$2 (2), S25.D (DRAIN)
OUTPUT_26: OUTPUT_BANK_3.P$3 (3), S26.D (DRAIN)
OUTPUT_27: OUTPUT_BANK_3.P$4 (4), S27.D (DRAIN)
OUTPUT_28: OUTPUT_BANK_3.P$5 (5), S28.D (DRAIN)
OUTPUT_29: OUTPUT_BANK_3.P$6 (6), S29.D (DRAIN)
OUTPUT_30: OUTPUT_BANK_3.P$7 (7), S30.D (DRAIN)
OUTPUT_31: OUTPUT_BANK_3.P$8 (8), S31.D (DRAIN)
OUTPUT_EN: R179.1, U5.13 (OE), U6.13 (OE), U7.13 (OE), U8.13 (OE), U39.13 (OE), U40.13 (OE), U41.13 (OE), U42.13 (OE), U81.5 (RST)
PWR_EN: PC_POWER_SUPPLY.8, SW2.2
PWR_LED: D4.A, R186.1
RELAY_PWR_DRAIN: D5.A, EM1.5, U84.3 (COLLECTOR)
RES: C7.2, R176.1, RESET.2 (B), U1.7 (RES')
RTS: C7.1, U2.2 (RTS#)
RW: R11.1, SD1.8 (RW)
RX: U1.37 (P30), U2.4 (RXD)
RXLED: R2.1, U2.14 (CBUS1)
SCL: R4.1, U1.35 (P28), U4.6 (SCL), U75.4 (I/O2B), U83.1 (SCL)
SCL_OUT: AUX.7, U75.6 (I/O1B)
SDA: R5.1, U1.36 (P29), U4.5 (SDA), U75.3 (I/O2A), U83.2 (SDA)
SDA_OUT: AUX.6, U75.1 (I/O1A)
SD_CS: R10.1, SD1.7 (CS), U1.44 (P3)
SD_DI: R9.1, SD1.6 (DI), U1.43 (P2)
SD_DO: R7.1, SD1.2 (D0), U1.41 (P0)
SD_SCLK: R8.1, SD1.4 (SCLK), U1.42 (P1)
SEG0: SEG1.10 (A), U40.15 (Q0)
SEG1: SEG1.9 (B), U40.1 (Q1)
SEG2: SEG1.8 (C), U40.3 (Q3)
SEG3: SEG1.5 (D), U40.7 (Q7)
SEG4: SEG1.4 (E), U40.6 (Q6)
SEG5: SEG1.2 (F), U40.4 (Q4)
SEG6: SEG1.3 (G), U40.5 (Q5)
SEG7: SEG1.7 (DP), U40.2 (Q2)
SEG8: SEG2.10 (A), U41.15 (Q0)
SEG9: SEG2.9 (B), U41.1 (Q1)
SEG10: SEG2.8 (C), U41.3 (Q3)
SEG11: SEG2.5 (D), U41.7 (Q7)
SEG12: SEG2.4 (E), U41.6 (Q6)
SEG13: SEG2.2 (F), U41.4 (Q4)
SEG14: SEG2.3 (G), U41.5 (Q5)
SEG15: SEG2.7 (DP), U41.2 (Q2)
SEG16: SEG3.10 (A), U42.15 (Q0)
SEG17: SEG3.9 (B), U42.1 (Q1)
SEG18: SEG3.8 (C), U42.3 (Q3)
SEG19: SEG3.5 (D), U42.7 (Q7)
SEG20: SEG3.4 (E), U42.6 (Q6)
SEG21: SEG3.2 (F), U42.4 (Q4)
SEG22: SEG3.3 (G), U42.5 (Q5)
SERVO_0: SERVO_0.1, U39.15 (Q0)
SERVO_1: SERVO_1.1, U39.1 (Q1)
SERVO_2: SERVO_2.1, U39.2 (Q2)
SERVO_3: SERVO_3.1, U39.3 (Q3)
SERVO_4: SERVO_4.1, U39.4 (Q4)
SERVO_5: SERVO_5.1, U39.5 (Q5)
SERVO_6: SERVO_6.1, U39.6 (Q6)
SERVO_7: SERVO_7.1, U39.7 (Q7)
SERVO_EXT: J36.2, SERVO_EXT_PWR.P$2 (2)
SERVO_PWR: C65.POS, J36.OUT, SERVO_0.2, SERVO_1.2, SERVO_2.2, SERVO_3.2, SERVO_4.2, SERVO_5.2, SERVO_6.2, SERVO_7.2
SIO_0: U1.19 (P16), U36.5 (SI/SIO0)
SIO_1: U1.20 (P17), U36.2 (SO/SIO1)
SIO_2: U1.21 (P18), U36.3 (SIO2)
SIO_3: U1.22 (P19), U36.7 (SIO3)
SIO_4: U1.23 (P20), U37.5 (SI/SIO0)
SIO_5: U1.24 (P21), U37.2 (SO/SIO1)
SIO_6: U1.25 (P22), U37.3 (SIO2)
SIO_7: U1.26 (P23), U37.7 (SIO3)
SOLENOID_GND: C62.N (NEG), C63.N (NEG), C64.N (NEG), R182.1, R183.1, S0.S (SOURCE), S1.S (SOURCE), S2.S (SOURCE), S3.S (SOURCE), S4.S (SOURCE), S5.S (SOURCE), S6.S (SOURCE), S7.S (SOURCE), S8.S (SOURCE), S9.S (SOURCE), S10.S (SOURCE), S11.S (SOURCE), S12.S (SOURCE), S13.S (SOURCE), S14.S (SOURCE), S15.S (SOURCE), S16.S (SOURCE), S17.S (SOURCE), S18.S (SOURCE), S19.S (SOURCE), S20.S (SOURCE), S21.S (SOURCE), S22.S (SOURCE), S23.S (SOURCE), S24.S (SOURCE), S25.S (SOURCE), S26.S (SOURCE), S27.S (SOURCE), S28.S (SOURCE), S29.S (SOURCE), S30.S (SOURCE), S31.S (SOURCE), SOLENOID_PWR.2, SOLENOID_PWR.3
SOLENOID_PWR: C62.P (POS), C63.P (POS), C64.P (POS), EM1.1, OUTPUT_BANK_0.P$9 (9), OUTPUT_BANK_1.P$9 (9), OUTPUT_BANK_2.P$9 (9), OUTPUT_BANK_3.P$9 (9)
SOLENOID_PWR_IN: FUSE.2A, FUSE.2B, SOLENOID_PWR.1, SOLENOID_PWR.4
SOL_PWR_RELAY: EM1.3, FUSE.1A, FUSE.1B
SOL_PWR_RELAY_CTRL: R188.1, R189.1, SEG3.7 (DP), U42.2 (Q2)
SRAM_CLK_0: U1.15 (P14), U36.6 (SCK)
SRAM_CLK_1: U1.16 (P15), U37.6 (SCK)
TX: U1.38 (P31), U2.1 (TXD)
TXLED: R3.1, U2.7 (CBUS2)
USBDM: R180.1, U2.9 (USBDM)
USBDP: R181.1, U2.8 (USBDP)
VBUS: C1.1, D1.A, D2.A, D3.A, U2.12 (VCC), U3.5 (VB), USB.1 (5V)
V_LED: C66.2, C67.2, C68.2, C69.2, J35.OUT, LIGHT_BANK_0.10, LIGHT_BANK_1.10, LIGHT_BANK_2.10, LIGHT_BANK_3.10, LIGHT_BANK_4.10, LIGHT_BANK_5.10, LIGHT_BANK_6.10, LIGHT_BANK_7.10
X0: U1.29 (X0), X1.1
X1: U1.28 (X1), X1.3

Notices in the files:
parts and their libraries:
PP_Aesthetics: (c) 2013 Longhorn Engineer
